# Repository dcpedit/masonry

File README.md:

# Masonry Keyboard

Inspired by [Bruce the Keyboard](https://www.jlw-kb.com/products/bruce-the-keyboard-the-pcb), this is a 12 column version with a less aggressive stagger.

Schematic for the STM32F072 integration was taken from Sleepdealer's [OSFRL project](https://github.com/Sleepdealr/OSFRL)

Here are the supported layouts:
[Keyboard Layout Editor](http://www.keyboard-layout-editor.com/#/gists/711e40adc1aee2aae4437fc2fe2fa7aa)

## Ordering PCBs from JLCPCB

The files needed for https://jlcpcb.com are located in the production folder:

* `pcb/production`

Once `pcb.zip` has been uploaded, you can continue with the selected default options. You can optionally change the solder mask color, which changes the final color of your PCB.

When using their assembly service, you will need to upload the following files separately:

* `bom.csv`
* `positions.csv`

These files were all generated with Fabrication Toolkit for KiCad: https://github.com/bennymeg/Fabrication-Toolkit

## Stacked Acrylic Case

Case file is in the `assets` folder.

### Parts List
| Description | Qty | Notes |
| ----------- | --- | ----- |
| 3mm acrylic | 7 | Qty = number of case layers
| 1.5mm acrylic | 1 | Switch plate
| M3x20mm chicago bolt | 6 | [Link](https://www.aliexpress.us/item/2251832451307213.html)
| M3x10mm chicago bolt | 1 | [Link](https://www.aliexpress.us/item/2251832451307213.html)
| M3x6mm screw | 1 - 6 | [Link](https://www.aliexpress.us/item/2255800885711092.html)
| M2x4mm round standoff | 7 | [Link](https://www.aliexpress.us/item/2251832782591461.html)
| M2x3mm screw | 7 | [Link](https://www.aliexpress.us/item/2255800480170108.html)
| M2x4mm screw | 7 | [Link](https://www.aliexpress.us/item/2255800480170108.html)
| 1mm EVA foam | 1 | Case foam
| 1.5mm EVA foam | 1 | Switch plate foam, [link](https://www.aliexpress.us/item/3256804208838525.html)
| 2mm EVA foam | 1 | Switch plate foam
| MX Switch | 38 - 44 |
| Adhesive rubber feet | 4 

Keycap sizes will depend on the layout you're building (refer to KLE layout above).  Blank uniform-profile keycaps works really great for this keyboard since the keys have a vertical orientation.  I found my blank XDA PBT keycaps on AliExpress.  The specific ones I use in my build were purchased [here (1u - 2u)](https://www.aliexpress.us/item/3256804203440964.html) and [here (3u)](https://www.aliexpress.us/item/3256801190573750.html).

| Keycap | Qty |
| ------ | --- |
| 1u | 18 - 28
| 1.25u | 8
| 1.5u | 4
| 1.75u | 4
| 2u | 0 - 4
| 3u | 0 - 2

### Assembly

The M3 hardware is for the keyboard case.  The shorter M3 fastener goes above the USB connector.  You will need to use a wafer head (flat) screw on the bottom to keep the port clear for the USB cable.  You can optionally use the same M3x6mm wafer head screws for the entire bottom of the case instad of the chicago bolt ones, which is what I did for my build.

The M2 hardware is to fasten the PCB to the case.  The M2x3mm screws go on the bottom, and the M2x4mm screws go on the top (PCB side), with the M2x4mm standoff extending through the bottom of the case.  The PCB is essentially floating vertically, but is held up by the 1mm case foam.  Below is simple diagram of how everything fits together.

### Firmware

QMK/VIA source:
https://github.com/qmk/qmk_firmware/tree/master/keyboards/dcpedit/masonry

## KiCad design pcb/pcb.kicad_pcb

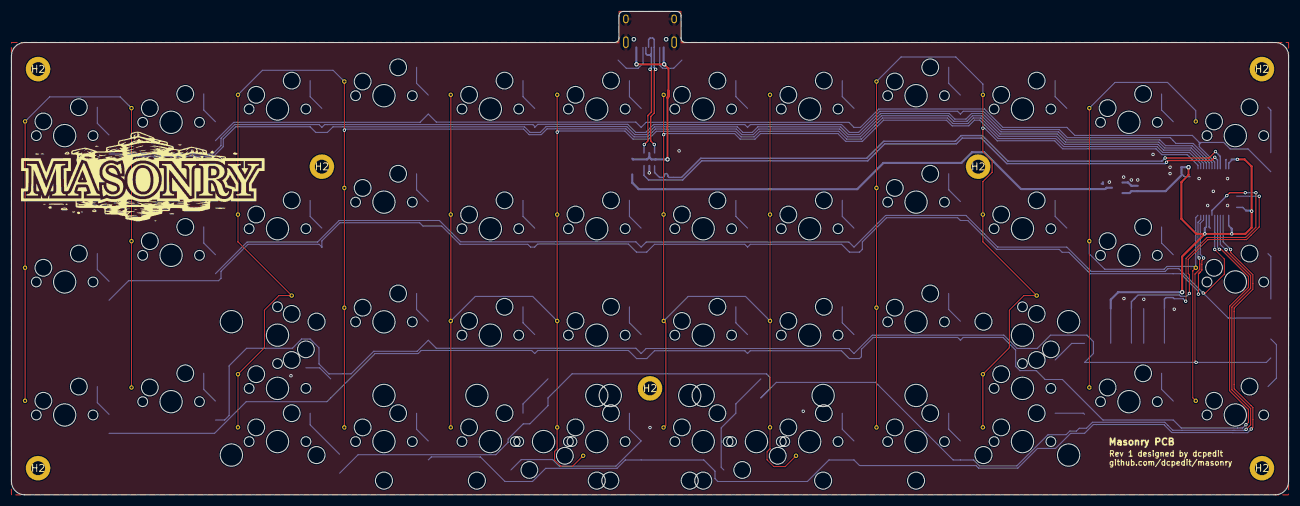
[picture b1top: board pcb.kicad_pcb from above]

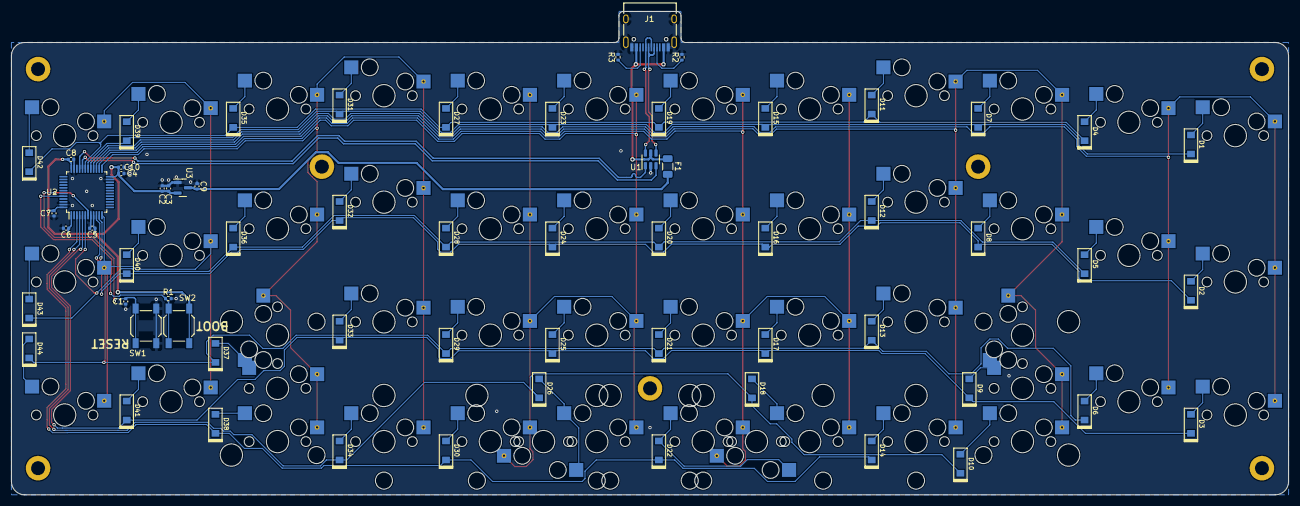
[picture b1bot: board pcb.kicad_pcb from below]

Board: 2 copper layers, 228.6 x 86.5 mm, 119 parts (64 on the bottom side), 70 nets.

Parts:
C1, C4, C5, C6, C7, C8: 100nF; C_0402_1005Metric
C2: 4.7uF; C_0402_1005Metric
C3, C9, C10: 1uF; C_0402_1005Metric
D1, D2, D3, D4, D5, D6, D7, D8, D9, D10, D11, D12, D13, D14, D15, D16, D17, D18, D19, D20, D21, D22, D23, D24, D25, D26, D27, D28, D29, D30, D31, D32, D33, D34, D35, D36, D37, D38, D39, D40, D41, D42, D43, D44: 1n4148; D_SOD123
F1: 500mA; Fuse_1206_3216Metric
H2, H2#2, H2#3, H2#4, H2#5, H2#6, H2#7: (no value)
J1: USB_C_Receptacle_USB2.0; USB_C_Receptacle_HRO_TYPE-C-31-M-12
MX00, MX25, MX45, MX60: MXOnly-1.75U-Hotswap-Vertical
MX01, MX02, MX03, MX24, MX42, MX43, MX44, MX61: MXOnly-1.25U-Hotswap-Vertical
MX04, MX10, MX11, MX12, MX13, MX14, MX15, MX21, MX22, MX23, MX31, MX32, MX33, MX34, MX41, MX50, MX51, MX52, MX53, MX54, MX55, MX62, MX63, MX64, MX71, MX72, MX73, MX74: MXOnly-1U-Hotswap
MX05, MX20, MX40, MX65: MXOnly-1.5U-Hotswap-Vertical
MX21.2: MXOnly-2U-Hotswap-ReversedVerticalStabilizers
MX33.2, MX72.2: MXOnly-2U-Hotswap
MX64.2: MXOnly-2U-Hotswap-VerticalStabilizers
R1: 10k; R_0402_1005Metric
R2, R3: 5k1; R_0402_1005Metric
SW1, SW2: RST; SW_SPST_SKQG_WithoutStem
U1: USBLC6-2SC6; SOT-23-6
U2: STM32F072C8Tx; LQFP-48_7x7mm_P0.5mm
U3: XC6206PxxxMR-Regulator_Linear; SOT-23

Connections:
+3V3: C2.1, C3.1, C4.1, C5.1, C6.1, C7.1, C8.1, C10.2, SW2.1, U2.1 (VBAT), U2.9 (VDDA), U2.24 (VDD), U2.36 (VDDIO2), U2.48 (VDD), U3.2 (VO)
+5V: C9.2, F1.2, U3.3 (VI)
/CC1: J1.A5 (CC1), R2.1
/CC2: J1.B5 (CC2), R3.1
BOOT0: R1.1, SW2.2, U2.44 (BOOT0)
COL0: MX00.1 (COL), MX10.1 (COL), MX20.1 (COL), MX40.1 (COL), MX50.1 (COL), MX60.1 (COL), U2.29 (PA8)
COL1: MX01.1 (COL), MX11.1 (COL), MX21.1 (COL), MX21.2.1 (COL), MX31.1 (COL), MX41.1 (COL), MX51.1 (COL), MX61.1 (COL), MX71.1 (COL), U2.28 (PB15)
COL2: MX02.1 (COL), MX12.1 (COL), MX22.1 (COL), MX32.1 (COL), MX42.1 (COL), MX52.1 (COL), MX62.1 (COL), MX72.1 (COL), MX72.2.1 (COL), U2.27 (PB14)
COL3: MX03.1 (COL), MX13.1 (COL), MX23.1 (COL), MX33.1 (COL), MX33.2.1 (COL), MX43.1 (COL), MX53.1 (COL), MX63.1 (COL), MX73.1 (COL), U2.26 (PB13)
COL4: MX04.1 (COL), MX14.1 (COL), MX24.1 (COL), MX34.1 (COL), MX44.1 (COL), MX54.1 (COL), MX64.1 (COL), MX64.2.1 (COL), MX74.1 (COL), U2.25 (PB12)
COL5: MX05.1 (COL), MX15.1 (COL), MX25.1 (COL), MX45.1 (COL), MX55.1 (COL), MX65.1 (COL), U2.12 (PA2)
D_N: U1.3 (I/O2), U2.32 (PA11)
D_P: U1.1 (I/O1), U2.33 (PA12)
D_USB_+: J1.A6 (D+), J1.B6 (D+), U1.6 (I/O1)
D_USB_-: J1.A7 (D-), J1.B7 (D-), U1.4 (I/O2)
GND: C1.1, C2.2, C3.2, C4.2, C5.2, C6.2, C7.2, C8.2, C9.1, C10.1, J1.A1 (GND), J1.A12 (GND), J1.B1 (GND), J1.B12 (GND), J1.S1 (SHIELD), R1.2, R2.2, R3.2, SW1.1, U1.2 (GND), U2.8 (VSSA), U2.23 (VSS), U2.35 (VSS), U2.47 (VSS), U3.1 (GND)
NRST: C1.2, SW1.2, U2.7 (NRST)
unnamed: D1.2 (A), MX00.2 (ROW)
unnamed: D2.2 (A), MX10.2 (ROW)
unnamed: D3.2 (A), MX20.2 (ROW)
unnamed: D4.2 (A), MX40.2 (ROW)
unnamed: D5.2 (A), MX50.2 (ROW)
unnamed: D6.2 (A), MX60.2 (ROW)
unnamed: D7.2 (A), MX01.2 (ROW)
unnamed: D8.2 (A), MX11.2 (ROW)
unnamed: D9.2 (A), MX21.2 (ROW), MX21.2.2 (ROW)
unnamed: D10.2 (A), MX31.2 (ROW)
unnamed: D11.2 (A), MX41.2 (ROW)
unnamed: D12.2 (A), MX51.2 (ROW)
unnamed: D13.2 (A), MX61.2 (ROW)
unnamed: D14.2 (A), MX71.2 (ROW)
unnamed: D15.2 (A), MX02.2 (ROW)
unnamed: D16.2 (A), MX12.2 (ROW)
unnamed: D17.2 (A), MX22.2 (ROW)
unnamed: D18.2 (A), MX32.2 (ROW)
unnamed: D19.2 (A), MX42.2 (ROW)
unnamed: D20.2 (A), MX52.2 (ROW)
unnamed: D21.2 (A), MX62.2 (ROW)
unnamed: D22.2 (A), MX72.2 (ROW), MX72.2.2 (ROW)
unnamed: D23.2 (A), MX03.2 (ROW)
unnamed: D24.2 (A), MX13.2 (ROW)
unnamed: D25.2 (A), MX23.2 (ROW)
unnamed: D26.2 (A), MX33.2 (ROW), MX33.2.2 (ROW)
unnamed: D27.2 (A), MX43.2 (ROW)
unnamed: D28.2 (A), MX53.2 (ROW)
unnamed: D29.2 (A), MX63.2 (ROW)
unnamed: D30.2 (A), MX73.2 (ROW)
unnamed: D31.2 (A), MX04.2 (ROW)
unnamed: D32.2 (A), MX14.2 (ROW)
unnamed: D33.2 (A), MX24.2 (ROW)
unnamed: D34.2 (A), MX34.2 (ROW)
unnamed: D35.2 (A), MX44.2 (ROW)
unnamed: D36.2 (A), MX54.2 (ROW)
unnamed: D37.2 (A), MX64.2 (ROW), MX64.2.2 (ROW)
unnamed: D38.2 (A), MX74.2 (ROW)
unnamed: D39.2 (A), MX05.2 (ROW)
unnamed: D40.2 (A), MX15.2 (ROW)
unnamed: D41.2 (A), MX25.2 (ROW)
unnamed: D42.2 (A), MX45.2 (ROW)
unnamed: D43.2 (A), MX55.2 (ROW)
unnamed: D44.2 (A), MX65.2 (ROW)
ROW0: D1.1 (K), D7.1 (K), D15.1 (K), D23.1 (K), D31.1 (K), D39.1 (K), U2.30 (PA9)
ROW1: D2.1 (K), D8.1 (K), D16.1 (K), D24.1 (K), D32.1 (K), D40.1 (K), U2.10 (PA0)
ROW2: D3.1 (K), D9.1 (K), D17.1 (K), D25.1 (K), D33.1 (K), D41.1 (K), U2.5 (PF0)
ROW3: D10.1 (K), D18.1 (K), D26.1 (K), D34.1 (K), U2.4 (PC15)
ROW4: D4.1 (K), D11.1 (K), D19.1 (K), D27.1 (K), D35.1 (K), D42.1 (K), U2.31 (PA10)
ROW5: D5.1 (K), D12.1 (K), D20.1 (K), D28.1 (K), D36.1 (K), D43.1 (K), U2.6 (PF1)
ROW6: D6.1 (K), D13.1 (K), D21.1 (K), D29.1 (K), D37.1 (K), D44.1 (K), U2.11 (PA1)
ROW7: D14.1 (K), D22.1 (K), D30.1 (K), D38.1 (K), U2.3 (PC14)
VBUS: F1.1, J1.A4 (VBUS), J1.A9 (VBUS), J1.B4 (VBUS), J1.B9 (VBUS), U1.5 (VBUS)

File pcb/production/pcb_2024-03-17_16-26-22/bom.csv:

Designator,Footprint,Quantity,Value,LCSC Part #
"C1, C4, C5, C6, C7, C8",0402,6,100nF,C307331
"C10, C3, C9",0402,3,1uF,C52923
C2,0402,1,4.7uF,C52923
"D1, D10, D11, D12, D13, D14, D15, D16, D17, D18, D19, D2, D20, D21, D22, D23, D24, D25, D26, D27, D28, D29, D3, D30, D31, D32, D33, D34, D35, D36, D37, D38, D39, D4, D40, D41, D42, D43, D44, D5, D6, D7, D8, D9",D_SOD123,44,1n4148,C81598
F1,1206,1,500mA,C70076
"H2_7, H2_6, H2_5, H2_4, H2_3, H2_2, H2",,7,,
J1,USB_C_Receptacle_HRO_TYPE-C-31-M-12,1,USB_C_Receptacle_USB2.0,C165948
"MX00, MX25, MX45, MX60",MXOnly-1.75U-Hotswap-Vertical,4,~,
"MX01, MX02, MX03, MX24, MX42, MX43, MX44, MX61",MXOnly-1.25U-Hotswap-Vertical,8,~,
"MX04, MX10, MX11, MX12, MX13, MX14, MX15, MX21, MX22, MX23, MX31, MX32, MX33, MX34, MX41, MX50, MX51, MX52, MX53, MX54, MX55, MX62, MX63, MX64, MX71, MX72, MX73, MX74",MXOnly-1U-Hotswap,28,~,
"MX05, MX20, MX40, MX65",MXOnly-1.5U-Hotswap-Vertical,4,~,
MX21.2,MXOnly-2U-Hotswap-ReversedVerticalStabilizers,1,~,
"MX33.2, MX72.2",MXOnly-2U-Hotswap,2,~,
MX64.2,MXOnly-2U-Hotswap-VerticalStabilizers,1,~,
R1,0402,1,10k,C25744
"R2, R3",0402,2,5k1,C25905
"SW1, SW2",SW_SPST_SKQG_WithoutStem,2,RST,C318884
U1,SOT-23-6,1,USBLC6-2SC6,C2827654
U2,LQFP-48_7x7mm_P0.5mm,1,STM32F072C8Tx,C80488
U3,SOT-23,1,XC6206PxxxMR-Regulator_Linear,C5446

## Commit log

2024-04-15 Add proper readme
2024-04-15 Add dxf
2024-04-16 Add firmware
